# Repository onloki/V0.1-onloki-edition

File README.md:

# V0.1-onloki-edition
Just me, who modified the optics of my V0.1

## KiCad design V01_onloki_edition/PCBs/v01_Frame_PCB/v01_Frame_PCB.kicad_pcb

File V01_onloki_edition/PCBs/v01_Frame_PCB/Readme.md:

# V0.1 Frame PCB

This PCB is heavily inspired by the original V0_Umbilical by timmi99 (https://github.com/timmit99/Voron-Hardware/tree/V0-Umbilical/V0-Umbilical). 

NOTE: I just took the footprint, so pinout and placemend of the connectors is different!

# BOM

For the PCB:
- 1x Molex 43045-1400 (Microfit 2x7) 
- 8x JST XH 2 Pin, XH2P ST
- 5x JST XH 4 Pin, XH4P ST
- 1x Screw Terminal with 5mm Pitch

Connectors for the cabels:
- 1x Molex 43045-1412 (Microfit 2x7)
- 8x JST PH 2 Pin, XH2P BU (NEMA 14 A and B motor comes often with JST XH 4pin conector, so if you do not want to cut them, you need only 6 connectors)
- 5x JST PH 4 Pin, XH4P BU
- 2x crimp ferrules for your wire

But you need also the connectors for your mcu...

# Pinout

Pinout graphics will come soon...

# Cover

There is a Cover to preventing the cables and PFTE to hit the timing belt.

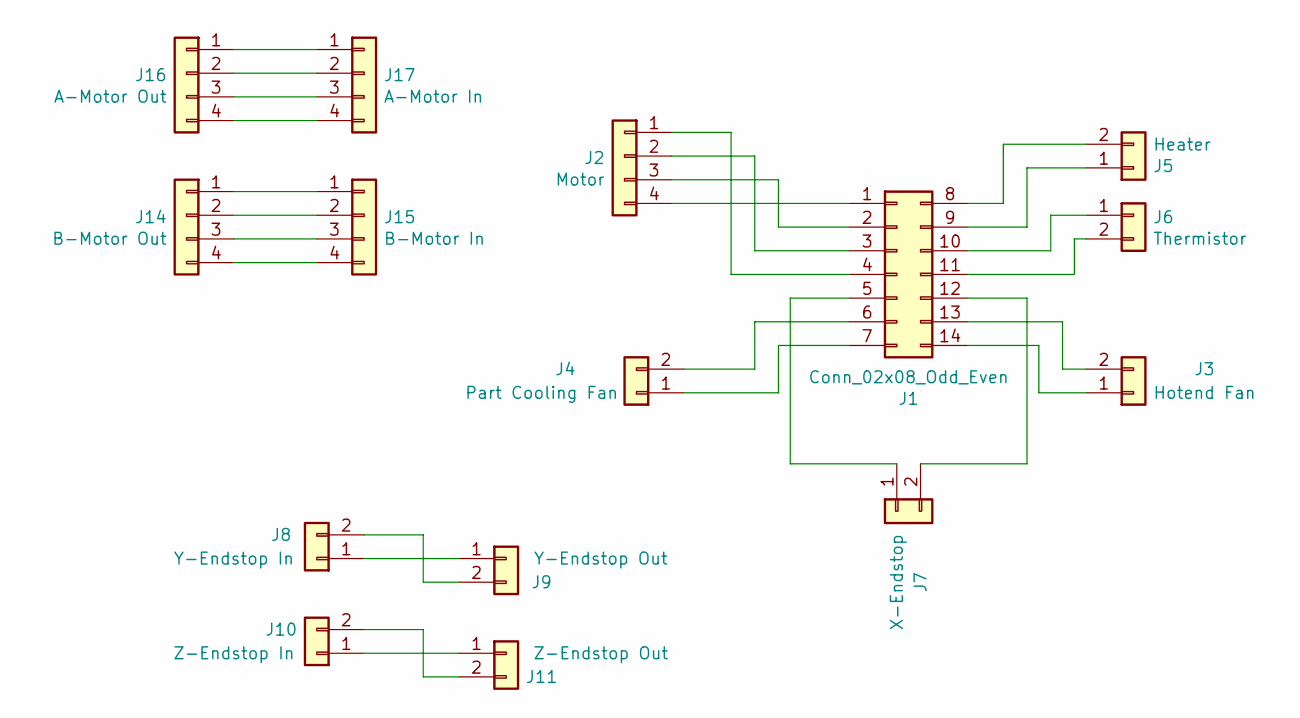
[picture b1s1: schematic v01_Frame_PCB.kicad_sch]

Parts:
J1: Conn_02x08_Odd_Even; Molex_Micro-Fit_3.0_43045-1412_2x07_P3.00mm_Vertical
J2: Motor; JST_XH_B4B-XH-A_1x04_P2.50mm_Vertical
J3: Hotend Fan; JST_XH_B2B-XH-A_1x02_P2.50mm_Vertical
J4: Part Cooling Fan; JST_XH_B2B-XH-A_1x02_P2.50mm_Vertical
J5: Heater; TerminalBlock_Phoenix_MKDS-1,5-2-5.08_1x02_P5.08mm_Horizont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
J6: Thermistor; JST_XH_B2B-XH-A_1x02_P2.50mm_Vertical
J7: X-Endstop; JST_XH_B2B-XH-A_1x02_P2.50mm_Vertical
J8: Y-Endstop In; JST_XH_B2B-XH-A_1x02_P2.50mm_Vertical
J9: Y-Endstop Out; JST_XH_B2B-XH-A_1x02_P2.50mm_Vertical
J10: Z-Endstop In; JST_XH_B2B-XH-A_1x02_P2.50mm_Vertical
J11: Z-Endstop Out; JST_XH_B2B-XH-A_1x02_P2.50mm_Vertical
J14: B-Motor Out; JST_XH_B4B-XH-A_1x04_P2.50mm_Vertical
J15: B-Motor In; JST_XH_B4B-XH-A_1x04_P2.50mm_Vertical
J16: A-Motor Out; JST_XH_B4B-XH-A_1x04_P2.50mm_Vertical
J17: A-Motor In; JST_XH_B4B-XH-A_1x04_P2.50mm_Vertical

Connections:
unnamed: J1.1, J2.4
unnamed: J1.2, J2.3
unnamed: J1.3, J2.2
unnamed: J1.4, J2.1
unnamed: J1.5, J7.1
unnamed: J1.6, J4.2
unnamed: J1.7, J4.1
unnamed: J1.8, J5.2
unnamed: J1.9, J5.1
unnamed: J1.10, J6.1
unnamed: J1.11, J6.2
unnamed: J1.12, J7.2
unnamed: J1.13, J3.2
unnamed: J1.14, J3.1
unnamed: J8.1, J9.1
unnamed: J8.2, J9.2
unnamed: J10.1, J11.1
unnamed: J10.2, J11.2
unnamed: J14.1, J15.1
unnamed: J14.2, J15.2
unnamed: J14.3, J15.3
unnamed: J14.4, J15.4
unnamed: J16.1, J17.1
unnamed: J16.2, J17.2
unnamed: J16.3, J17.3
unnamed: J16.4, J17.4

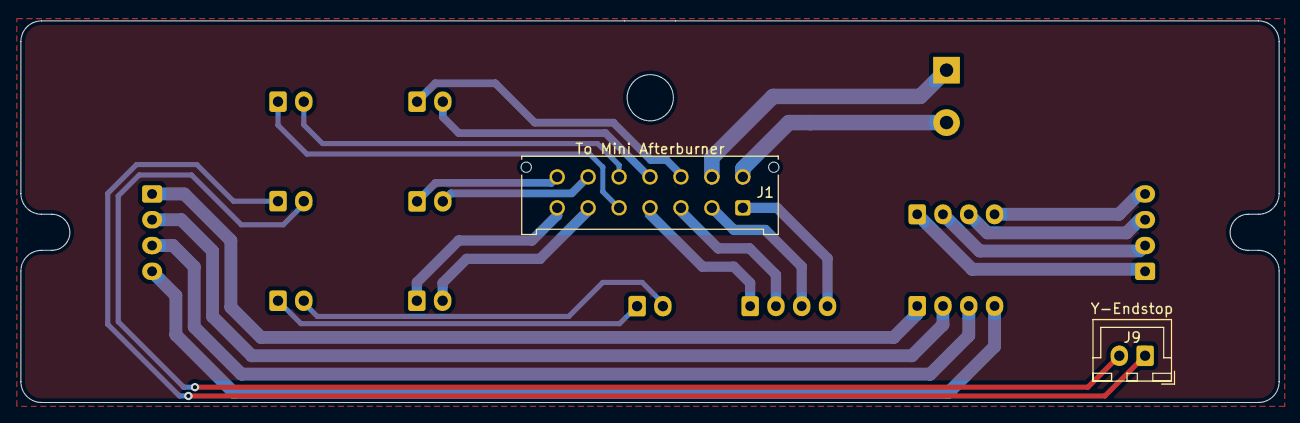
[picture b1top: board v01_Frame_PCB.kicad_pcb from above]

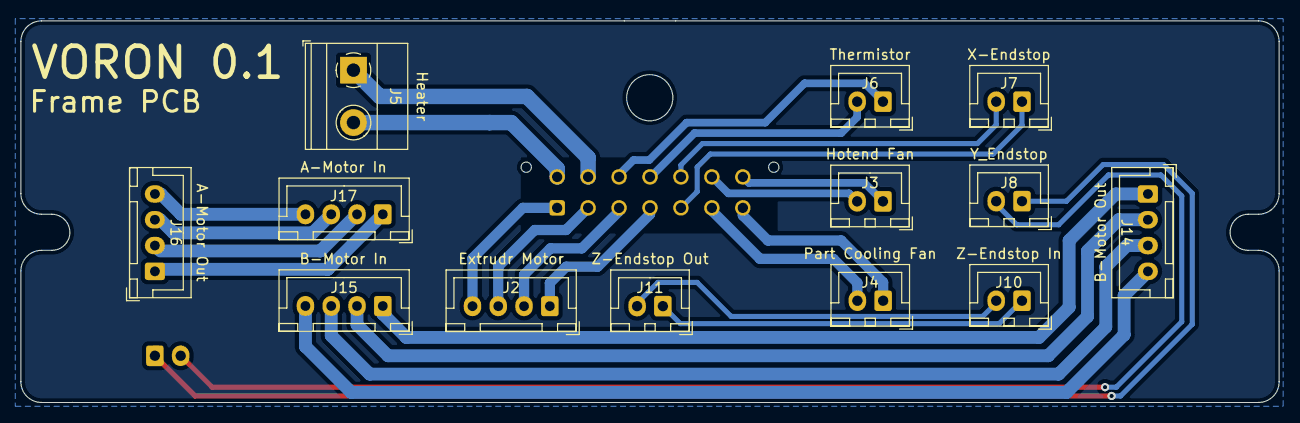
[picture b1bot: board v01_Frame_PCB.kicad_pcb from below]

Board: 2 copper layers, 122.0 x 37.0 mm, 15 parts (13 on the bottom side), 26 nets.

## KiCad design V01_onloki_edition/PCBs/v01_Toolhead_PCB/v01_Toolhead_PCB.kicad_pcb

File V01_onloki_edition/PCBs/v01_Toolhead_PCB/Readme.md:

# V0.1 Toolhead PCB

Inspired by the Pancake board by Christoph Müller (https://github.com/christophmuellerorg/voron_0_pancake_board). I just simplified the PCB for my needs.

NOTE: This is not a Pancake Board! It share only the same outer dimensions and placement of some connectors (differend Pinout!)

# BOM

For the PCB:
- 1x Molex 43045-1400 (Microfit 2x7) 
- 1x Molex 43045-0200 (Microfit 2x1)
- 5x JST PH 2 Pin, PH2P ST
- 1x JST PH 4 Pin, PH4P ST

Connectors for your cables:
- 1x Molex 43025-1400 (Microfit 2x7)
- 1x Molex 43025-0200 (Microfit 2x1)
- 5x JST PH 2 Pin, PH2P BU
- 1x JST PH 4 Pin, PH4P BU

# Pinout

Pinout graphics will come soon...

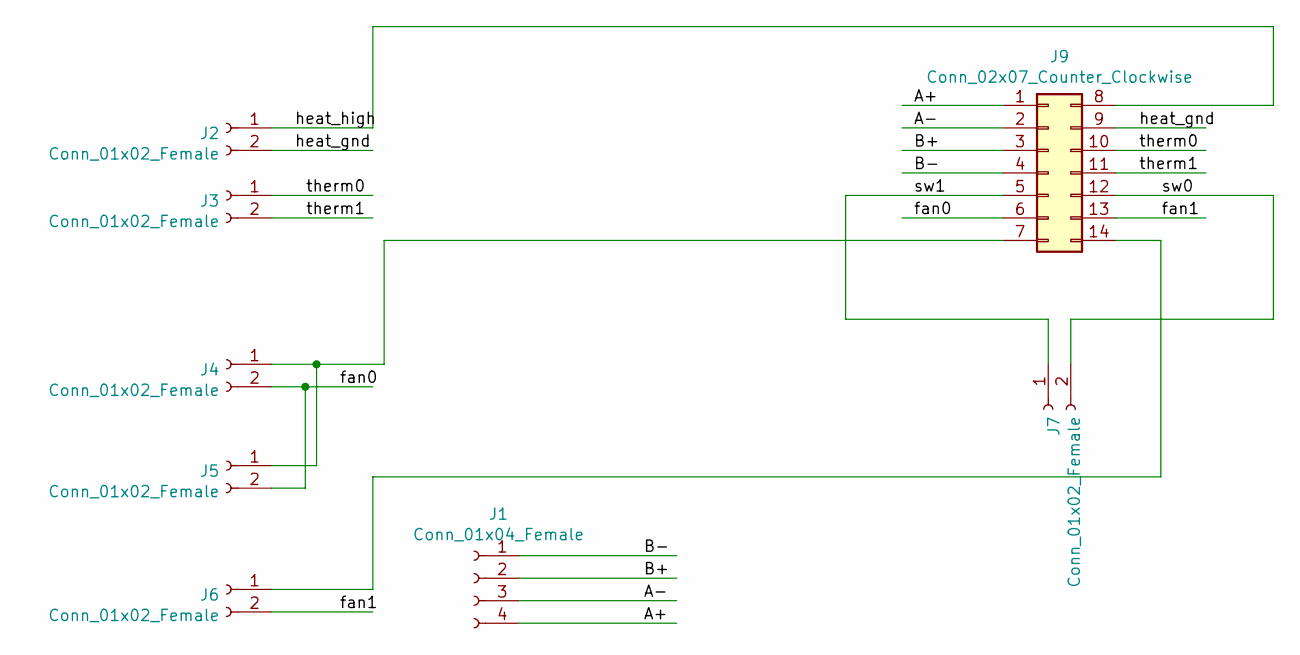
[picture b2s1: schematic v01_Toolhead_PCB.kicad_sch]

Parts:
J1: Conn_01x04_Female; JST_PH_B4B-PH-K_1x04_P2.00mm_Vertical
J2: Conn_01x02_Female; Molex_Micro-Fit_3.0_43045-0200_2x01_P3.00mm_Horizontal
J3, J4, J5, J6, J7: Conn_01x02_Female; JST_PH_B2B-PH-K_1x02_P2.00mm_Vertical
J9: Conn_02x07_Counter_Clockwise; Molex_Micro-Fit_3.0_43045-1400_2x07_P3.00mm_Horizontal

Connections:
/A+: J1.4, J9.1
/A-: J1.3, J9.2
/B+: J1.2, J9.3
/B-: J1.1, J9.4
/fan0: J4.2, J5.2, J9.6
/fan1: J6.2, J9.13
/heat_gnd: J2.2, J9.9
/heat_high: J2.1, J9.8
/sw0: J7.2, J9.12
/sw1: J7.1, J9.5
/therm0: J3.1, J9.10
/therm1: J3.2, J9.11
unnamed: J4.1, J5.1, J9.7
unnamed: J6.1, J9.14

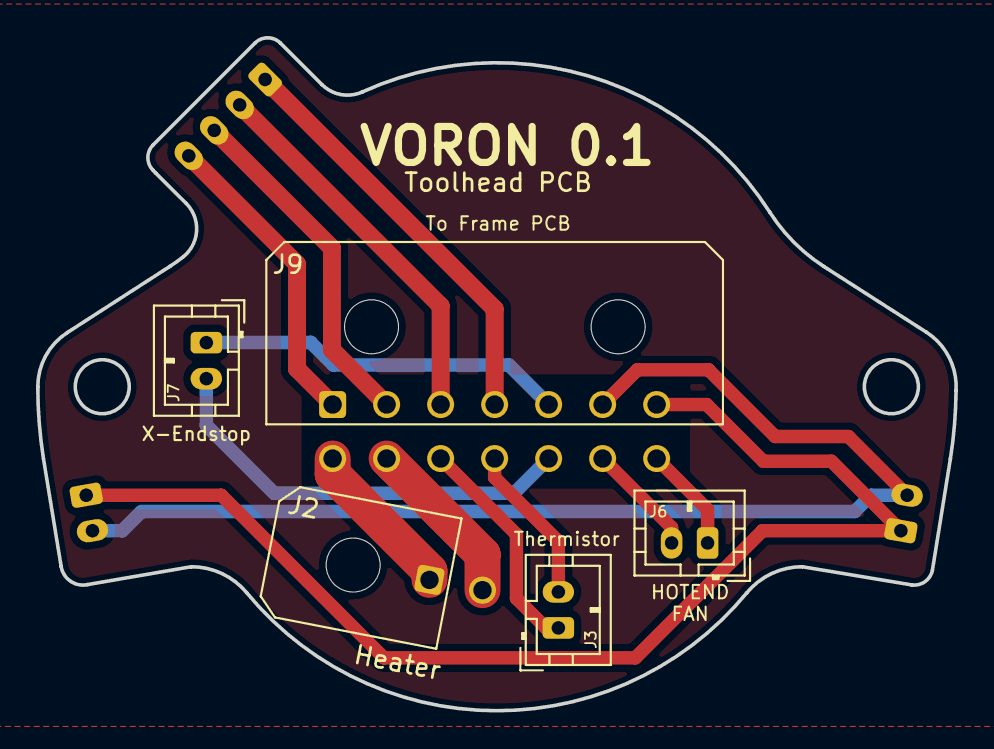
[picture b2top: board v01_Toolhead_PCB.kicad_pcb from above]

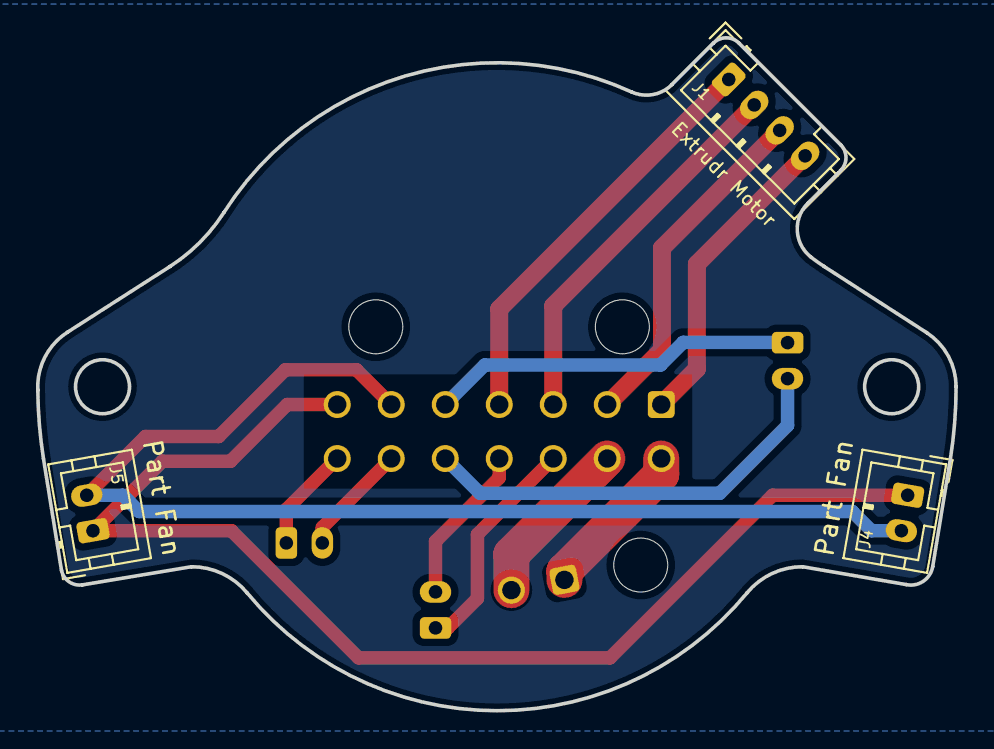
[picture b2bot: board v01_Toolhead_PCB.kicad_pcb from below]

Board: 2 copper layers, 51.0 x 37.4 mm, 8 parts (3 on the bottom side), 14 nets.

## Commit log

2022-02-12 Create REDME
2022-02-12 Rename REDME to REDME.md
2022-02-12 Rename REDME.md to Readme.md
